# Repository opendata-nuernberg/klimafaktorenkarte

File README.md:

# klimafaktorenkarte

## 11.11.2024 Update
- Moved hardware into [this separate repository](https://github.com/opendata-nuernberg/open-sensor-platform) to accomodate for firmware and v2 hardware revision.

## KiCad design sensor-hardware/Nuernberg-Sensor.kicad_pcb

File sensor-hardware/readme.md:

# Hardware

The board uses the ESP32-C3 microcontroller, which provides both WiFi and Bluetooth connectivity, as well as an integrated USB-JTAG adapter.

The system is powered from a USB Type-C port. The TLV62568DBV buck converter is used to supply the system with 3.3V.

As far as sensors are concerned, the SHT40 is used to measure temperature and humidity, and the DPS310 is used to measure the atmospheric pressure.

JLCPCB was used to manufacture and assemble the board. The jlcpcb folder contains the ordering files.

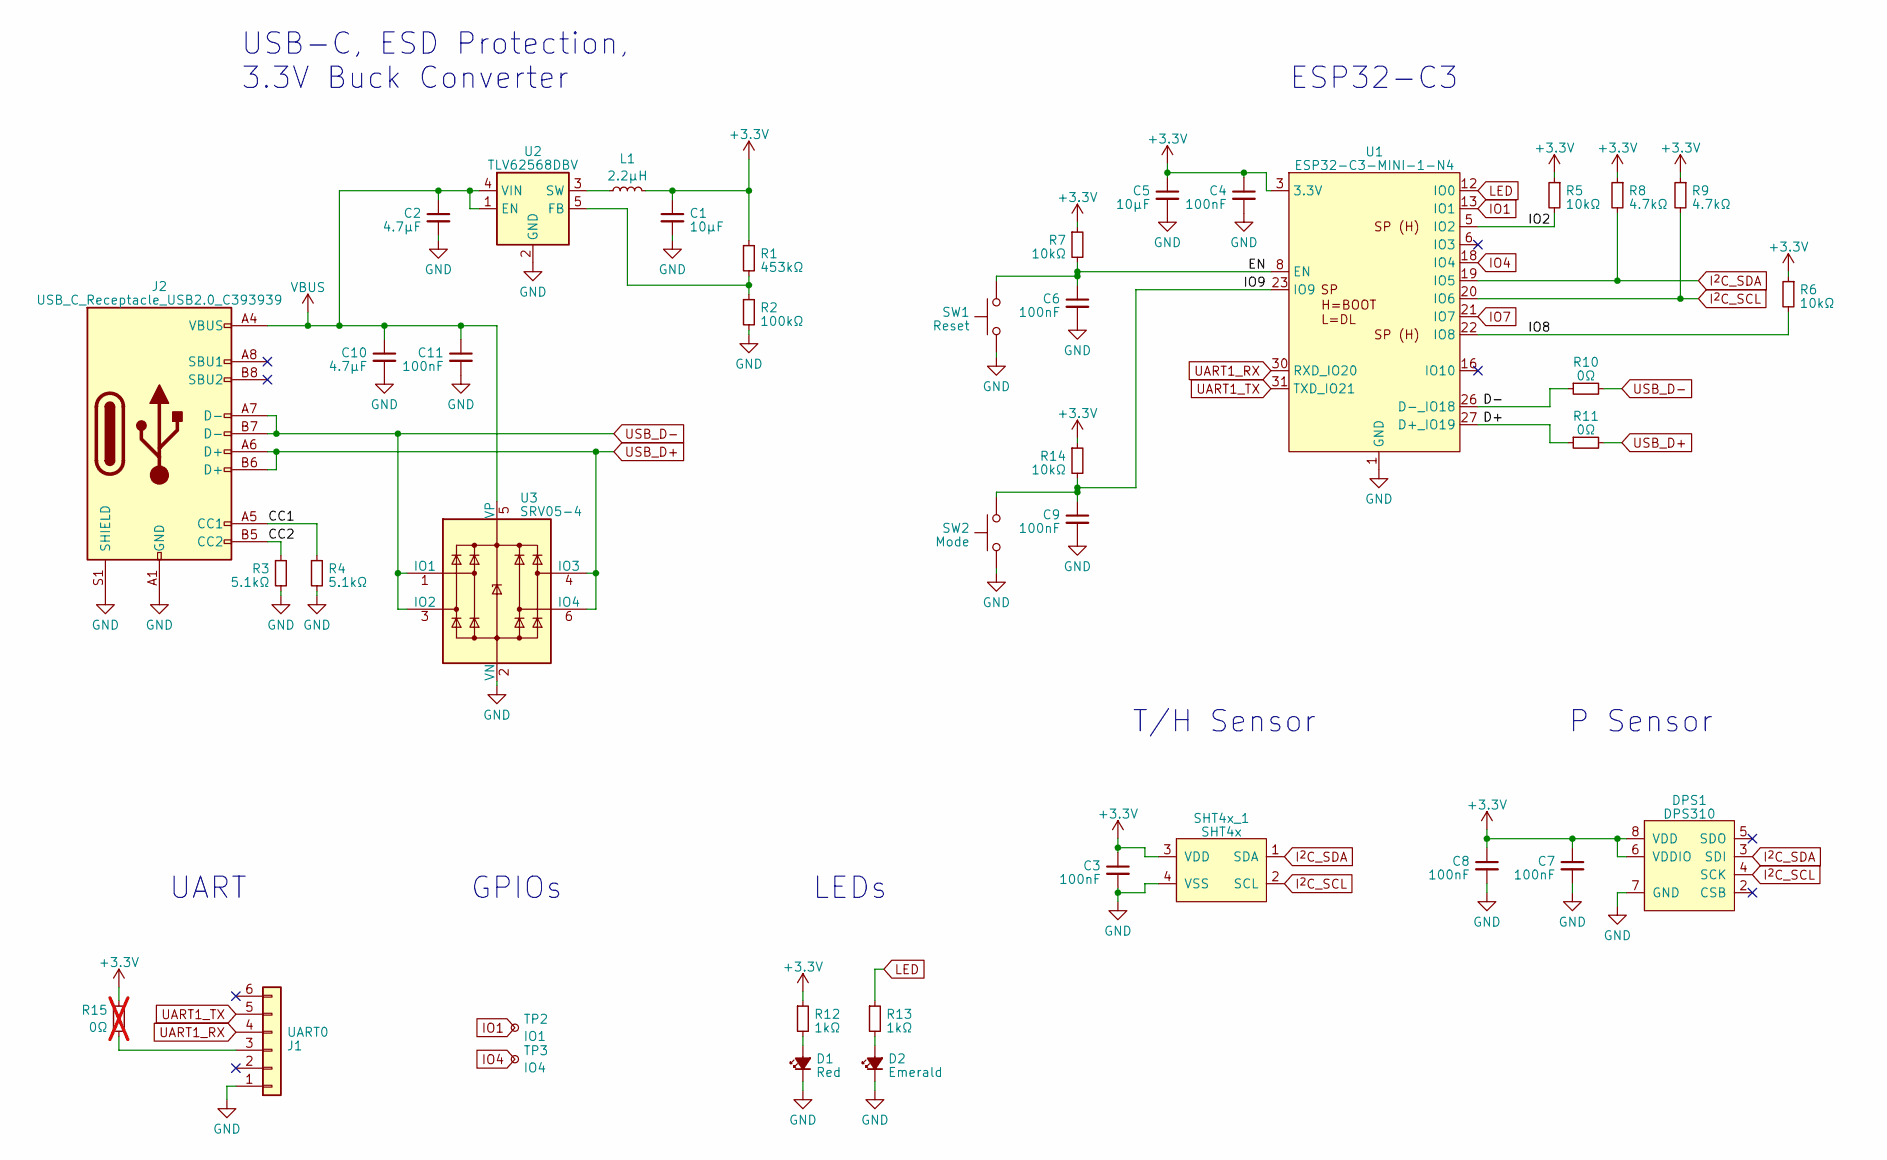
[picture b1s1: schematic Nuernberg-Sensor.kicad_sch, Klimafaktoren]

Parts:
C1, C5: 10µF; C_0603_1608Metric_NoSilk
C2, C10: 4.7µF; C_0603_1608Metric_NoSilk
C3, C4, C6, C7, C8, C9, C11: 100nF; C_0402_1005Metric_NoSilk
D1: Red; LED_0603_1608Metric_SmallSilk
D2: Emerald; LED_0603_1608Metric_SmallSilk
DPS1: DPS310; LCSC C130156
J1: UART0; PinHeader_1x06_P2.54mm_NoSilk_No3D
J2: USB_C_Receptacle_USB2.0_C393939; USB_C_Receptacle_C313131_TYPE-C-31-M-12; LCSC C2927038
L1: 2.2µH; L_FNR3015S; LCSC C167747
R1: 453kΩ; R_0402_1005Metric_NoSilk
R2: 100kΩ; R_0402_1005Metric_NoSilk
R3, R4: 5.1kΩ; R_0402_1005Metric_NoSilk
R5, R6, R7, R14: 10kΩ; R_0402_1005Metric_NoSilk
R8, R9: 4.7kΩ; R_0402_1005Metric_NoSilk
R10, R11: 0Ω; R_0402_1005Metric_NoSilk
R12, R13: 1kΩ; R_0402_1005Metric_NoSilk
R15: 0Ω; R_0402_1005Metric_NoSilk; not fitted
SHT4x_1: SHT4x; Sensirion_SHT4x; LCSC C2909890
SW1: Reset; TS-1187A-B-A-B; LCSC C318884
SW2: Mode; TS-1187A-B-A-B; LCSC C318884
TP2: IO1; TestPoint_Pad_D1.0mm_NoSIlk
TP3: IO4; TestPoint_Pad_D1.0mm_NoSIlk
U1: ESP32-C3-MINI-1-N4; ESP32-PICO-MINI-02-N8R2; LCSC C2838502
U2: TLV62568DBV; SOT-23-5_NoSilk; LCSC C163219
U3: SRV05-4; SOT-23-6_NoSilk; LCSC C7420376

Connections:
+3.3V: C1.1, C3.1, C4.1, C5.1, C7.1, C8.1, DPS1.6 (VDDIO), DPS1.8 (VDD), L1.2, R1.1, R5.1, R6.1, R7.1, R8.1, R9.1, R12.1, R14.1, R15.2, SHT4x_1.3 (VDD), U1.3 (3.3V)
/CC1: J2.A5 (CC1), R4.1
/CC2: J2.B5 (CC2), R3.1
/D+: R11.1, U1.27 (D+_IO19)
/D-: R10.1, U1.26 (D-_IO18)
/EN: C6.1, R7.2, SW1.2, U1.8 (EN)
/IO2: R5.2, U1.5 (IO2)
/IO8: R6.2, U1.22 (IO8)
/IO9: C9.1, R14.2, SW2.2, U1.23 (IO9)
GND: C1.2, C2.2, C3.2, C4.2, C5.2, C6.2, C7.2, C8.2, C9.2, C10.2, C11.2, D1.1 (K), D2.1 (K), DPS1.1 (GND), DPS1.7 (GND), J1.1, J2.A1 (GND), J2.A12 (GND), J2.B1 (GND), J2.B12 (GND), J2.S1 (SHIELD), R2.2, R3.2, R4.2, SHT4x_1.4 (VSS), SW1.1, SW2.1, U1.1 (GND), U1.2 (GND), U1.11 (GND), U1.14 (GND), U1.49 (GND), U2.2 (GND), U3.2 (VN)
IO1: TP2.1, U1.13 (IO1)
IO4: TP3.1, U1.18 (IO4)
IO7: U1.21 (IO7)
I^{2}C_SCL: DPS1.4 (SCK), R9.2, SHT4x_1.2 (SCL), U1.20 (IO6)
I^{2}C_SDA: DPS1.3 (SDI), R8.2, SHT4x_1.1 (SDA), U1.19 (IO5)
LED: R13.1, U1.12 (IO0)
unnamed: D1.2 (A), R12.2
unnamed: D2.2 (A), R13.2
unnamed: J1.3, R15.1
unnamed: R1.2, R2.1, U2.5 (FB)
unnamed: L1.1, U2.3 (SW)
UART1_RX: J1.4, U1.30 (RXD_IO20)
UART1_TX: J1.5, U1.31 (TXD_IO21)
USB_D+: J2.A6 (D+), J2.B6 (D+), R11.2, U3.4 (IO3), U3.6 (IO4)
USB_D-: J2.A7 (D-), J2.B7 (D-), R10.2, U3.1 (IO1), U3.3 (IO2)
VBUS: C2.1, C10.1, C11.1, J2.A4 (VBUS), J2.A9 (VBUS), J2.B4 (VBUS), J2.B9 (VBUS), U2.1 (EN), U2.4 (VIN), U3.5 (VP)

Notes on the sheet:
P Sensor
UART
USB-C, ESD Protection, 3.3V Buck Converter
LEDs
GPIOs
ESP32-C3
T/H Sensor

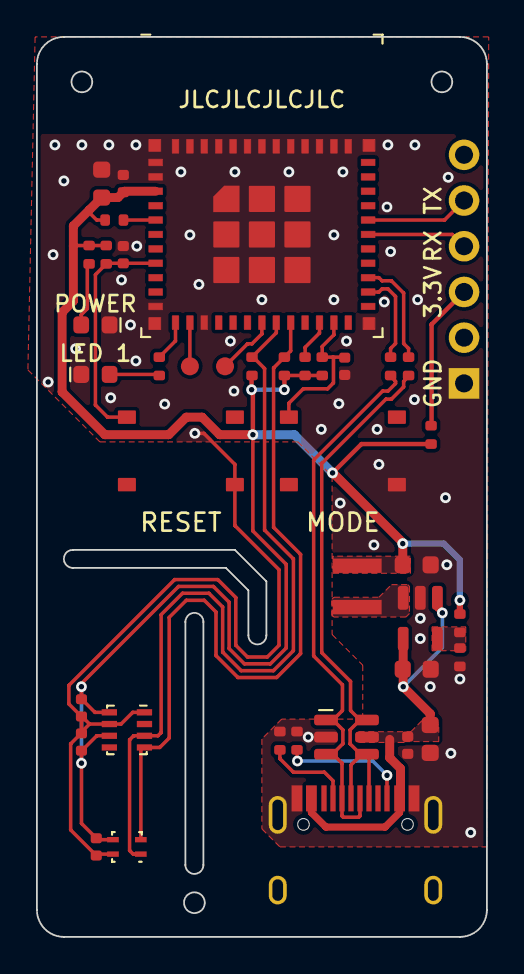
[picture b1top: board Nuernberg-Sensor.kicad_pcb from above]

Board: 2 copper layers, 25.0 x 50.0 mm, 40 parts (0 on the bottom side), 25 nets.

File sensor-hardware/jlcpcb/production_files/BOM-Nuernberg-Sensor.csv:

Comment,Designator,Footprint,LCSC
1kΩ,"R12,R13",R_0402_1005Metric_NoSilk,C11702
DPS310,DPS1,DPS310,C130156
100nF,"C11,C3,C4,C6,C7,C8,C9",C_0402_1005Metric_NoSilk,C1525
TLV62568DBV,U2,SOT-23-5_NoSilk,C163219
2.2µH,L1,L_FNR3015S,C167747
0Ω,"R10,R11",R_0402_1005Metric_NoSilk,C17168
4.7µF,"C10,C2",C_0603_1608Metric_NoSilk,C19666
10µF,"C1,C5",C_0603_1608Metric_NoSilk,C19702
Red,D1,LED_0603_1608Metric_SmallSilk,C2286
100kΩ,R2,R_0402_1005Metric_NoSilk,C25741
10kΩ,"R14,R5,R6,R7",R_0402_1005Metric_NoSilk,C25744
4.7kΩ,"R8,R9",R_0402_1005Metric_NoSilk,C25900
5.1kΩ,"R3,R4",R_0402_1005Metric_NoSilk,C25905
ESP32-C3-MINI-1-N4,U1,ESP32-PICO-MINI-02-N8R2,C2838502
SHT4x,SHT4x_1,Sensirion_SHT4x,C2909890
USB_C_Receptacle_USB2.0_C393939,J2,USB_C_Receptacle_C313131_TYPE-C-31-M-12,C2927038
Reset,"SW1,SW2",TS-1187A-B-A-B,C318884
453kΩ,R1,R_0402_1005Metric_NoSilk,C321521
Emerald,D2,LED_0603_1608Metric_SmallSilk,C72043
SRV05-4,U3,SOT-23-6_NoSilk,C7420376

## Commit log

2023-09-13 inital structure with basic ui
2023-09-13 sensor converter
2023-09-13 empty api
2023-09-13 converter tool
2023-09-15 display h3 hexagon
2023-10-26 update ui
2023-11-02 h3 mac binaries
2023-11-02 init flutter package
2023-11-02 (add) green fields nwr working.
2023-11-02 (fix) moved to way -> way better ;-)
2023-11-02 (chore) minor refactor.
2023-11-03 (add) some more green key value pairs.
2023-11-03 (add) less dependencies better water, green broken.
2023-11-04 (add) new green data, seems to work with stable internet.
2023-12-11 added hardware files
2023-12-11 added readme and schematic to hardware folder
2024-11-11 (chore) moved hardware into separate repository https://github.com/opendata-nuernberg/open-sensor-platform
